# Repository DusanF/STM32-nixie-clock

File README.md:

# STM32 nixie clock
My take on nixie tube clock, using STM32G070 with internal RTC and four 74141 as drivers.
Clock uses Czechoslovak ZM1082T, but main board can by used with any nixie tubes.

## Firmware
Folder Nixie_clock contains STM32CubeIDE project. Firmware is written in C using STM32 HAL libraries. After peripherals are initialized, main loop starts with 100ms period. After checking state of buttons and reading current time from RTC, displayed time is updated if needed. Once every minute, cathode poisoning prevention routine is started, cycling through every digit for a few milliseconds, before settling at current time.

## Schematic + PCB
Folder contains KiCad project with schematic and PCB design. Schematic is also exported in pdf format.

Device is powered by 12V DC. With all 4 digits lit up, current draw is about 150mA. HV for nixies is generated by external step-up module, that can be bought cheaply on ebay, aliexpress, etc. 74141s are powered by 5V generated by 1117. MCU gets 3.3V stabilised only by zener diode from 5V rail. Oprional supercap for RTC backup is charged by MCU via integrated resistor (set in FW to 1k5).

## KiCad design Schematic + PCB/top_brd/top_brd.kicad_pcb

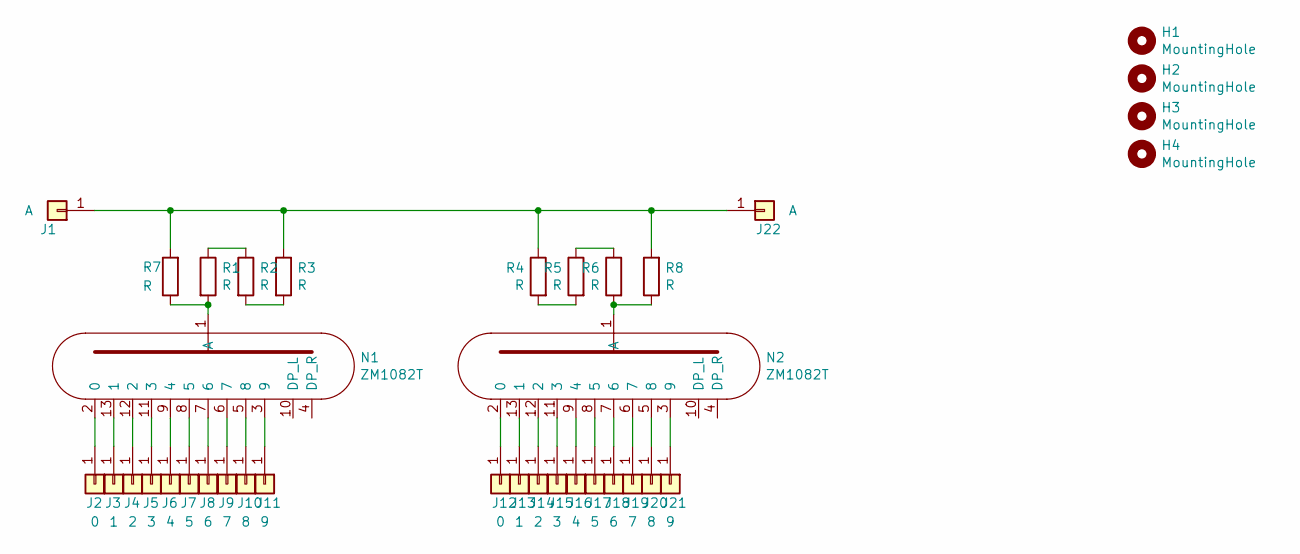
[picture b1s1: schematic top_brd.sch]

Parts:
H1, H2, H3, H4: MountingHole; MountingHole_3.2mm_M3
J1, J22: A; PinSocket_1x01_P2.54mm_Vertical
J2, J12: 0; PinSocket_1x01_P2.54mm_Vertical
J3, J13: 1; PinSocket_1x01_P2.54mm_Vertical
J4, J14: 2; PinSocket_1x01_P2.54mm_Vertical
J5, J15: 3; PinSocket_1x01_P2.54mm_Vertical
J6, J16: 4; PinSocket_1x01_P2.54mm_Vertical
J7, J17: 5; PinSocket_1x01_P2.54mm_Vertical
J8, J18: 6; PinSocket_1x01_P2.54mm_Vertical
J9, J19: 7; PinSocket_1x01_P2.54mm_Vertical
J10, J20: 8; PinSocket_1x01_P2.54mm_Vertical
J11, J21: 9; PinSocket_1x01_P2.54mm_Vertical
N1, N2: ZM1082T; CPA_14
R1, R2, R3, R4, R5, R6: R; R_0603_1608Metric
R7, R8: R; R_Axial_DIN0411_L9.9mm_D3.6mm_P12.70mm_Horizontal

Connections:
unnamed: J1.1, J22.1, R3.1, R4.1, R7.2, R8.2
unnamed: J2.1, N1.2 (0)
unnamed: J3.1, N1.13 (1)
unnamed: J4.1, N1.12 (2)
unnamed: J5.1, N1.11 (3)
unnamed: J6.1, N1.9 (4)
unnamed: J7.1, N1.8 (5)
unnamed: J8.1, N1.7 (6)
unnamed: J9.1, N1.6 (7)
unnamed: J10.1, N1.5 (8)
unnamed: J11.1, N1.3 (9)
unnamed: J12.1, N2.2 (0)
unnamed: J13.1, N2.13 (1)
unnamed: J14.1, N2.12 (2)
unnamed: J15.1, N2.11 (3)
unnamed: J16.1, N2.9 (4)
unnamed: J17.1, N2.8 (5)
unnamed: J18.1, N2.7 (6)
unnamed: J19.1, N2.6 (7)
unnamed: J20.1, N2.5 (8)
unnamed: J21.1, N2.3 (9)
unnamed: N1.1 (A), R1.2, R7.1
unnamed: N2.1 (A), R6.2, R8.1
unnamed: R1.1, R2.1
unnamed: R2.2, R3.2
unnamed: R4.2, R5.2
unnamed: R5.1, R6.1

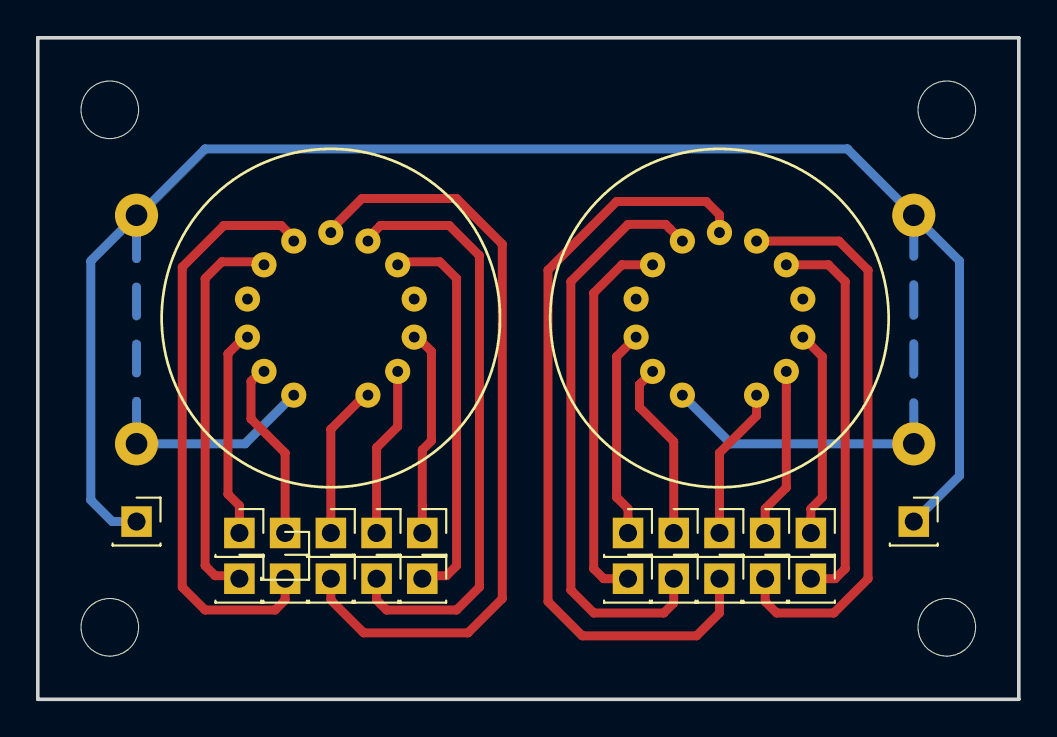
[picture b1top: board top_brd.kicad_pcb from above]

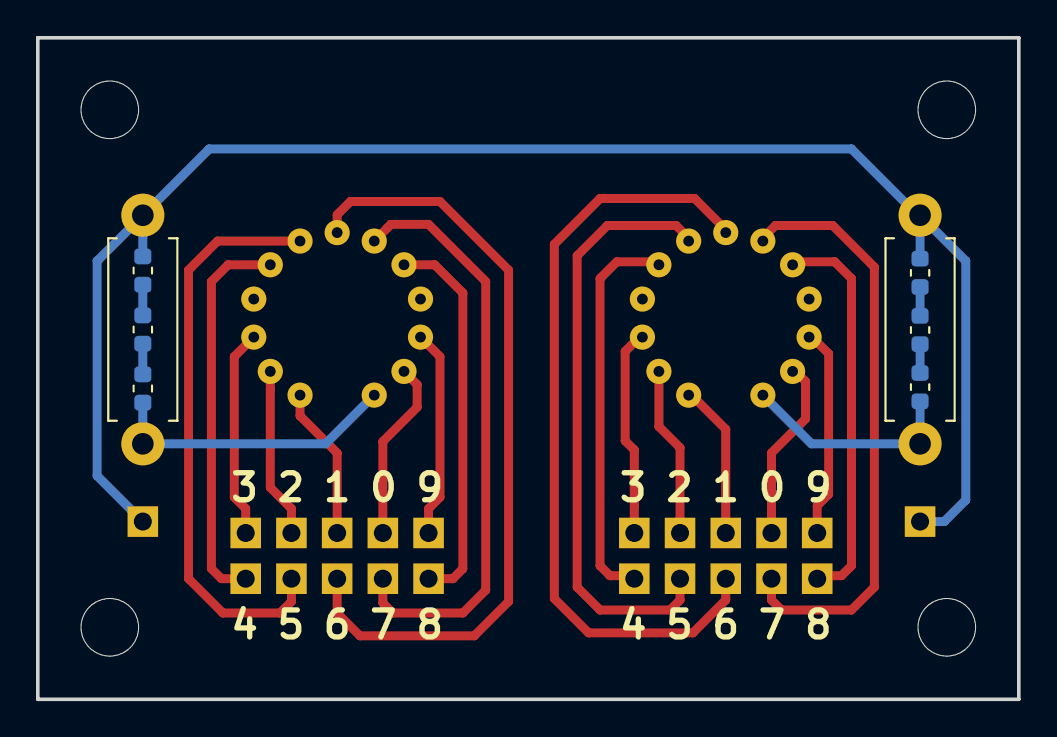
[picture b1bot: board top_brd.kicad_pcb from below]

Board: 2 copper layers, 54.5 x 36.8 mm, 36 parts (8 on the bottom side), 27 nets.

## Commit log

2021-05-26 Add sources
2021-05-26 Add schematic and PCB
2021-05-26 Add photos
